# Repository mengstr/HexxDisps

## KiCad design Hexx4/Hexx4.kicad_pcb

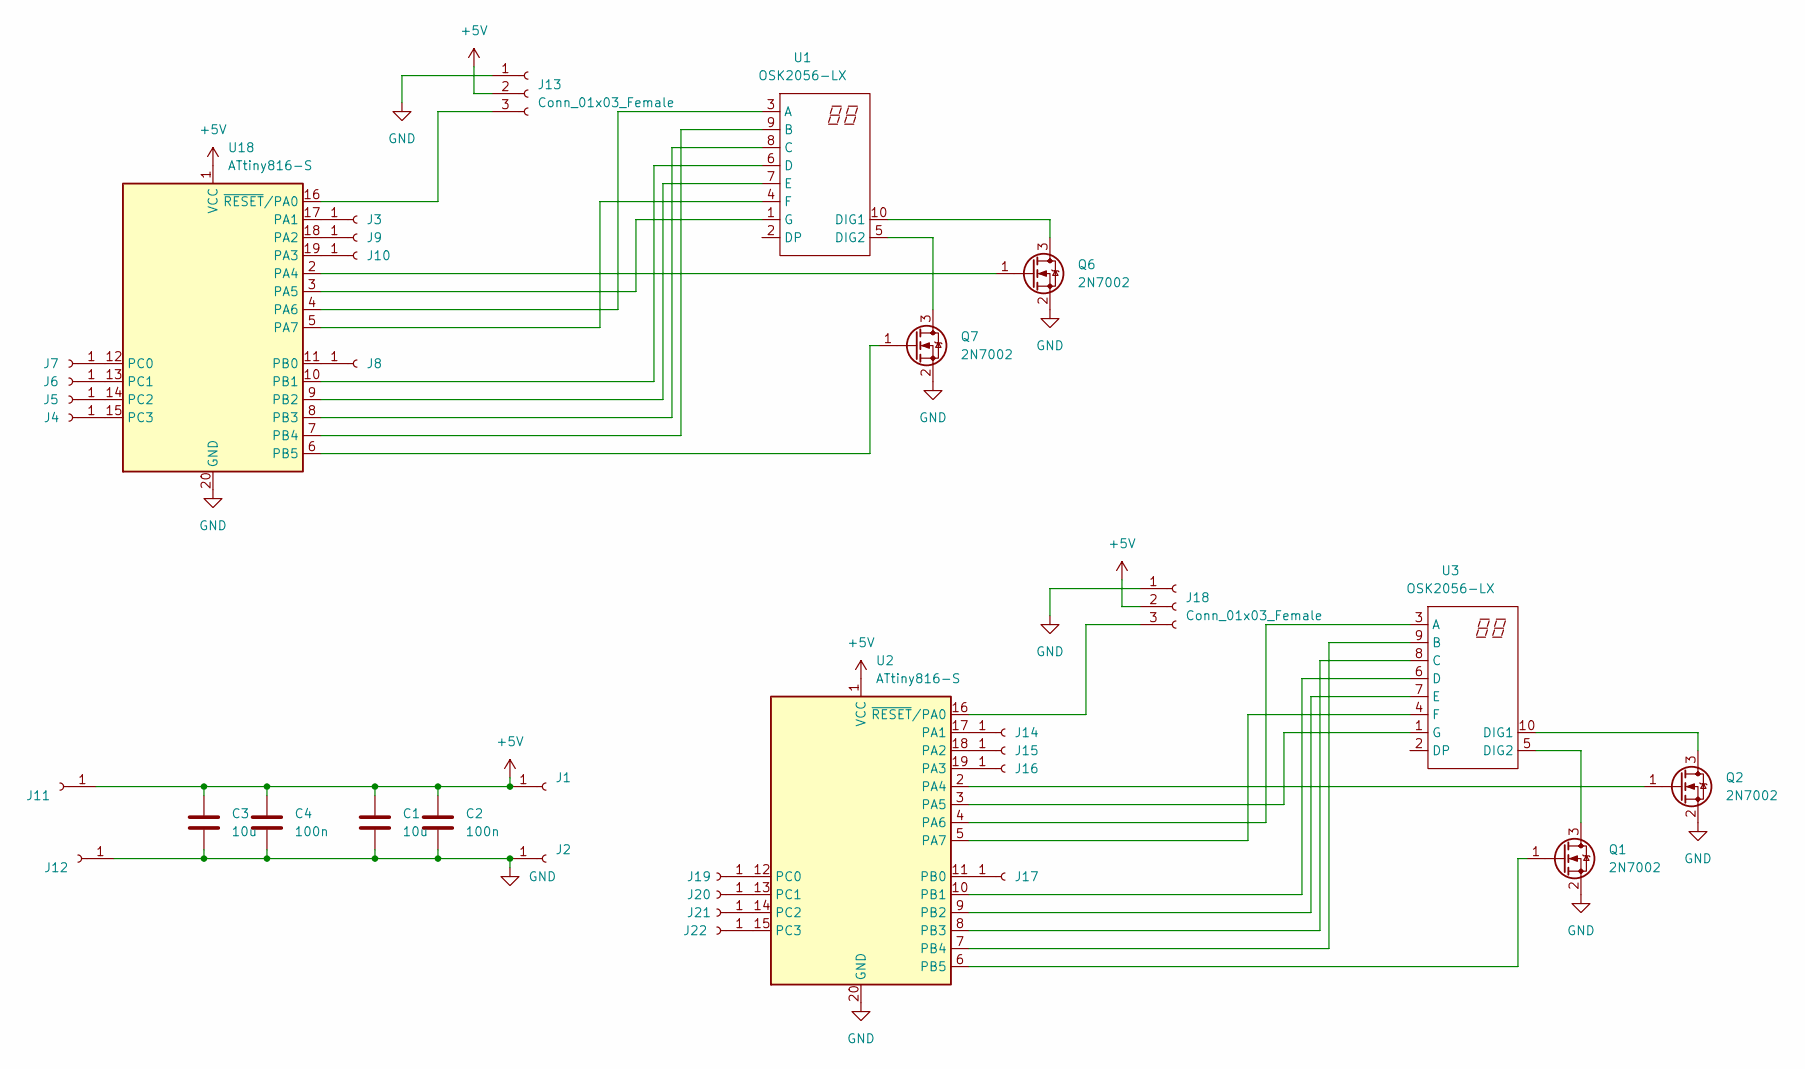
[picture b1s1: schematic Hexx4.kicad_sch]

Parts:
C1, C3: 10u; C_0805_2012Metric_Pad1.18x1.45mm_HandSolder
C2, C4: 100n; C_0805_2012Metric_Pad1.18x1.45mm_HandSolder
J1, J2, J3, J4, J5, J6, J7, J8, J9, J11, J12, J14, J15, J16, J19, J20, J21, J22: Conn_01x01_Female; PinHeader_1x01_P2.54mm_Vertical
J10, J17: Conn_01x01_Female; Pin_D1.0mm_L10.0mm
J13, J18: Conn_01x03_Female; PinSocket_1x03_P2.54mm_Vertical
Q1, Q2, Q6, Q7: 2N7002; SOT-23
U1, U3: OSK2056-LX; OSK2056
U2, U18: ATtiny816-S; SOIC-20W_7.5x12.8mm_P1.27mm

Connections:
+5V: C1.1, C2.1, C3.1, C4.1, J1.1, J11.1, J13.2, J18.2, U2.1 (VCC), U18.1 (VCC)
GND: C1.2, C2.2, C3.2, C4.2, J2.1, J12.1, J13.1, J18.1, Q1.2 (S), Q2.2 (S), Q6.2 (S), Q7.2 (S), U2.20 (GND), U18.20 (GND)
unnamed: J3.1, U18.17 (PA1)
unnamed: J4.1, U18.15 (PC3)
unnamed: J5.1, U18.14 (PC2)
unnamed: J6.1, U18.13 (PC1)
unnamed: J7.1, U18.12 (PC0)
unnamed: J8.1, U18.11 (PB0)
unnamed: J9.1, U18.18 (PA2)
unnamed: J10.1, U18.19 (PA3)
unnamed: J13.3, U18.16 (~RESET/PA0)
unnamed: J14.1, U2.17 (PA1)
unnamed: J15.1, U2.18 (PA2)
unnamed: J16.1, U2.19 (PA3)
unnamed: J17.1, U2.11 (PB0)
unnamed: J18.3, U2.16 (~RESET/PA0)
unnamed: J19.1, U2.12 (PC0)
unnamed: J20.1, U2.13 (PC1)
unnamed: J21.1, U2.14 (PC2)
unnamed: J22.1, U2.15 (PC3)
unnamed: Q1.1 (G), U2.6 (PB5)
unnamed: Q1.3 (D), U3.5 (DIG2)
unnamed: Q2.1 (G), U2.2 (PA4)
unnamed: Q2.3 (D), U3.10 (DIG1)
unnamed: Q6.1 (G), U18.2 (PA4)
unnamed: Q6.3 (D), U1.10 (DIG1)
unnamed: Q7.1 (G), U18.6 (PB5)
unnamed: Q7.3 (D), U1.5 (DIG2)
unnamed: U1.1 (G), U18.3 (PA5)
unnamed: U1.3 (A), U18.4 (PA6)
unnamed: U1.4 (F), U18.5 (PA7)
unnamed: U1.6 (D), U18.10 (PB1)
unnamed: U1.7 (E), U18.9 (PB2)
unnamed: U1.8 (C), U18.8 (PB3)
unnamed: U1.9 (B), U18.7 (PB4)
unnamed: U2.3 (PA5), U3.1 (G)
unnamed: U2.4 (PA6), U3.3 (A)
unnamed: U2.5 (PA7), U3.4 (F)
unnamed: U2.7 (PB4), U3.9 (B)
unnamed: U2.8 (PB3), U3.8 (C)
unnamed: U2.9 (PB2), U3.7 (E)
unnamed: U2.10 (PB1), U3.6 (D)

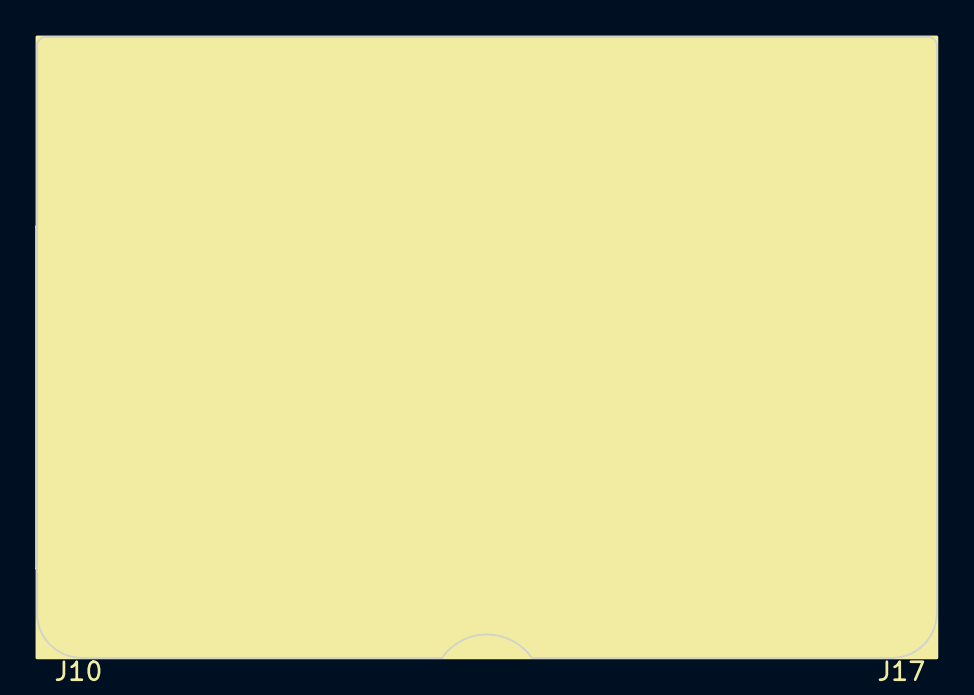
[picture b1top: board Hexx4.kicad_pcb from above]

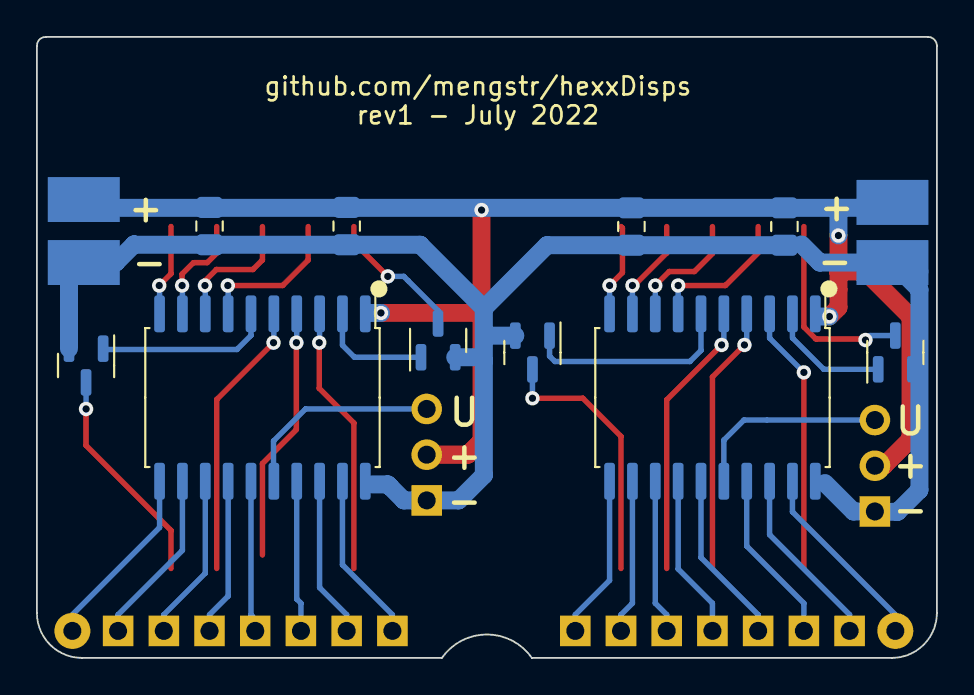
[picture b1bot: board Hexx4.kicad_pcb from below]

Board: 2 copper layers, 50.0 x 34.5 mm, 34 parts (10 on the bottom side), 42 nets.

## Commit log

2022-07-27 Initial checkin
